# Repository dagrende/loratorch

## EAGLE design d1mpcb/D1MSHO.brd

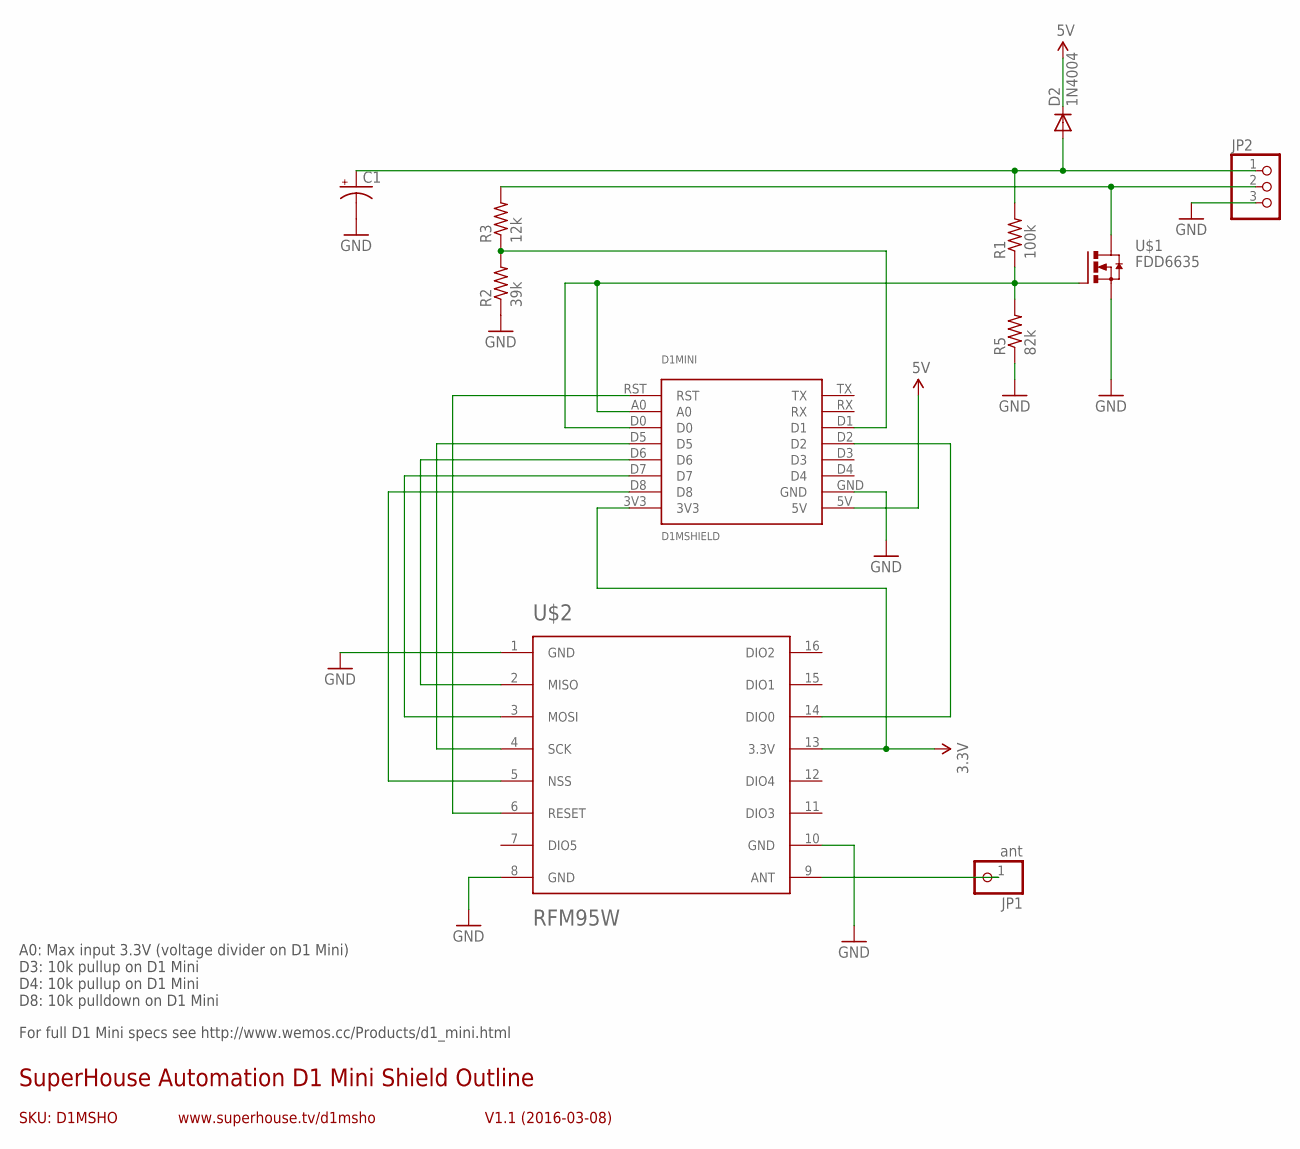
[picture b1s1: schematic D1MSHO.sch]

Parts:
C1: CPOL-USE3.5-8; E3,5-8
D1MINI: D1MSHIELD; D1MSHELD
D2: 1N4004; DO41-10
JP1: ant; 1X01
JP2: PINHD-1X3/90; 1X03/90
R1: 100k; M0805
R2: 39k; M0805
R3: 12k; M0805
R5: 82k; M0805
U$1: FDD6635; TO252
U$2: RFM95W; RFM

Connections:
3.3V: D1MINI.3V3, U$2.13 (3.3V)
5V: D1MINI.5V, D2.C
A0: D1MINI.A0, D1MINI.D0, R1.1, R5.2, U$1.1 (G)
ANT: JP1.1, U$2.9 (ANT)
D5: D1MINI.D5, U$2.4 (SCK)
D6: D1MINI.D6, U$2.2 (MISO)
D7: D1MINI.D7, U$2.3 (MOSI)
D8: D1MINI.D8, U$2.5 (NSS)
GND: C1.-, D1MINI.GND, JP2.3, R2.1, R5.1, U$1.2 (S), U$2.1 (GND), U$2.8 (GND), U$2.10 (GND)
unnamed: JP2.2, R3.2, U$1.3 (D)
unnamed: D1MINI.D1, R2.2, R3.1
unnamed: C1.+, D2.A, JP2.1, R1.2
unnamed: D1MINI.D2, U$2.14 (DIO0)
RST: D1MINI.RST, U$2.6 (RESET)

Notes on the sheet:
SKU: D1MSHO
SuperHouse Automation D1 Mini Shield Outline
V1.1 (2016-03-08)
www.superhouse.tv/d1msho
A0: Max input 3.3V (voltage divider on D1 Mini) D3: 10k pullup on D1 Mini D4: 10k pullup on D1 Mini D8: 10k pulldown on D1 Mini
For full D1 Mini specs see http://www.wemos.cc/Products/d1_mini.html

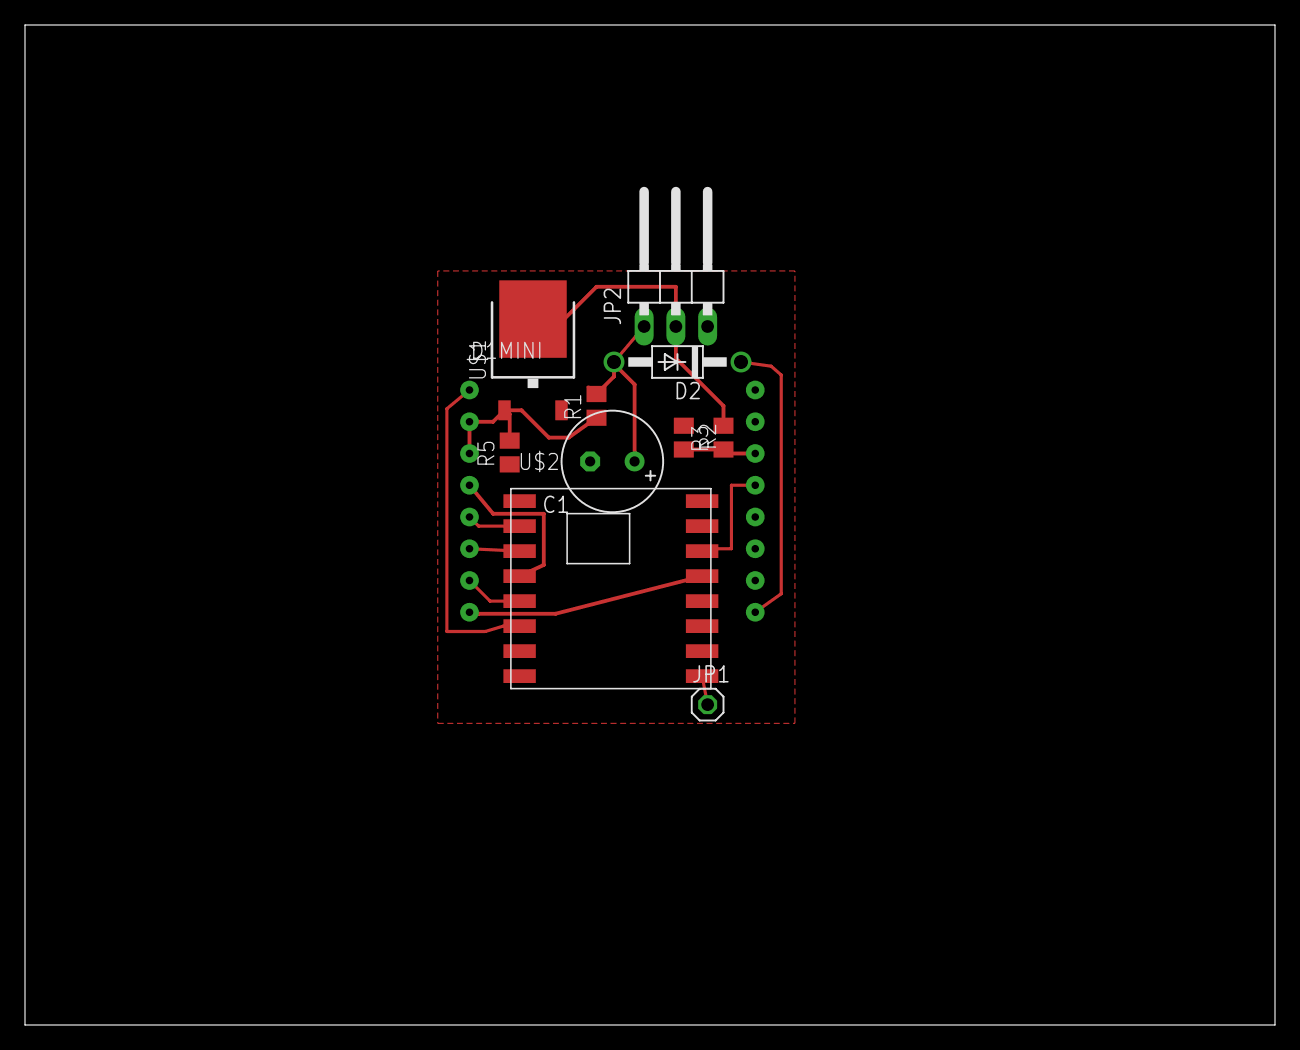
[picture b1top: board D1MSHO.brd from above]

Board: 2 copper layers, 100.0 x 80.0 mm, 11 parts (0 on the bottom side), 14 nets.

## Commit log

2017-05-23 initial
2017-05-28 added Button dependency, changed pin assignments for new circuitry, added lamp on button sensing and voltage measurement
2017-06-04 better init messages
2017-06-12 added torch pcb design - add-on card for Wemos d1 mini with power control, lamp-on-sesnor, battery voltage sensor, lora radio module
2017-08-13 new schematic and rx driver

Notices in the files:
parts and their libraries:
freetronics-original: Licensing: CC v3.0 Share-Alike You are welcome to use this library for commercial purposes.
